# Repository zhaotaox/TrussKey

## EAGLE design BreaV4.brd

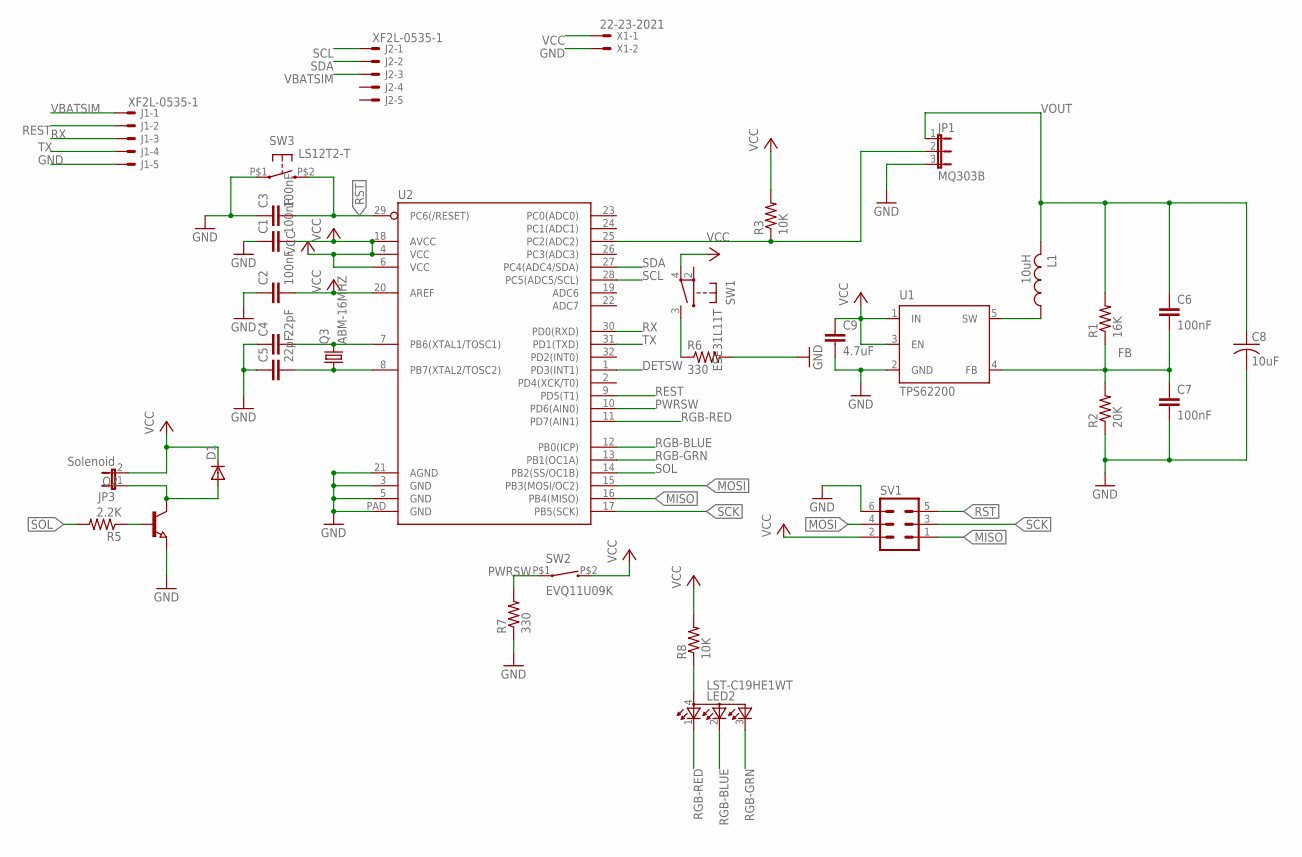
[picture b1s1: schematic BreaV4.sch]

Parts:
C1, C2, C3: 100nF; C0603
C4, C5: 22pF; C0603
C6, C7: 100nF; C0402
C8: 10uF; C0805K
C9: 4.7uF; C0402
D1: DIODE-SOD123; SOD123
J1, J2: XF2L-0535-1
JP1: MQ303B; JP2
JP3: Solenoid; JP1
L1: 10uH; L2825P
LED2: LST-C19HE1WT
Q2: NPN-TRANSISTOR_SOT23; SOT23
Q3: ABM-16MHZ
R1: 16K; R0402
R2: 20K; R0402
R3, R8: 10K; R0402
R5: 2.2K; R0402
R6, R7: 330; R0402
SV1: MA03-2
SW1: ESE31L11T; SWITCH
SW2: EVQ11U09K; EVQ11U-09K
SW3: LS12T2-T
U1: TPS62200
U2: ATMEGA328P_MLFMLF32; MLF32-PAD
X1: 22-23-2021

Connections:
DETSW: R6.1, SW1.3 (1), U2.1 (PD3(INT1))
FB: C6.2, C7.1, R1.1, R2.2, U1.4 (FB)
GND: C1.1, C2.1, C3.1, C4.1, C5.1, C7.2, C8.2, C9.2, J1.5 (MS), JP1.3, Q2.2 (E), R2.1, R6.2, R7.1, SV1.6 (MISO), SW3.P$1 (S1), U1.2 (GND), U2.3 (GND), U2.5 (GND), U2.21 (AGND), U2.PAD (GND), X1.2
MISO: SV1.1, U2.16 (PB4(MISO))
MOSI: SV1.4, U2.15 (PB3(MOSI/OC2))
unnamed: C5.2, Q3.P$1 (1), U2.8 (PB7(XTAL2/TOSC2))
unnamed: C4.2, Q3.P$2 (2), U2.7 (PB6(XTAL1/TOSC1))
unnamed: JP1.2, R3.1, U2.25 (PC2(ADC2))
unnamed: LED2.4 (A), R8.1
unnamed: D1.A, JP3.1, Q2.3 (C)
unnamed: Q2.1 (B), R5.1
PWRSW: R7.2, SW2.P$1 (1), U2.10 (PD6(AIN0))
REST: J1.2 (MS), U2.9 (PD5(T1))
RGB-BLUE: LED2.2 (CGREEN), U2.12 (PB0(ICP))
RGB-GRN: LED2.3 (CBLUE), U2.13 (PB1(OC1A))
RGB-RED: LED2.1 (CRED), U2.11 (PD7(AIN1))
RST: C3.2, SV1.5 (VTG), SW3.P$2 (S2), U2.29 (PC6(/RESET))
RX: J1.3 (MS), U2.30 (PD0(RXD))
SCK: SV1.3, U2.17 (PB5(SCK))
SCL: J2.1 (MSV), U2.28 (PC5(ADC5/SCL))
SDA: J2.2 (MS), U2.27 (PC4(ADC4/SDA))
SOL: R5.2, U2.14 (PB2(SS/OC1B))
SW: L1.1, U1.5 (SW)
TX: J1.4 (MS), U2.31 (PD1(TXD))
VBATSIM: J1.1 (MSV), J2.3 (MS)
VCC: C1.2, C2.2, C9.1, D1.C, JP3.2, R3.2, R8.2, SV1.2, SW1.4 (C3), SW2.P$2 (2), U1.1 (IN), U1.3 (EN), U2.4 (VCC), U2.6 (VCC), U2.18 (AVCC), U2.20 (AREF), X1.1
VOUT: C6.1, C8.1, JP1.1, L1.2, R1.2

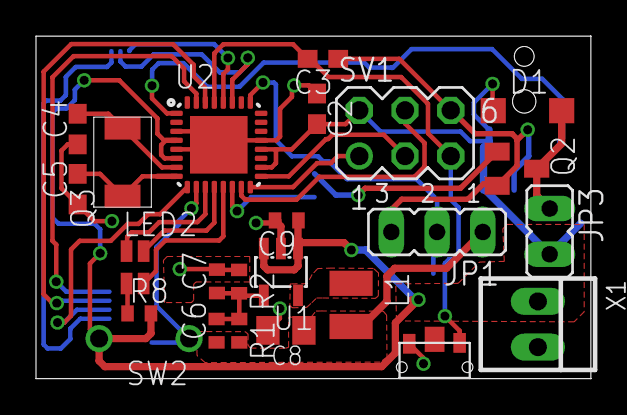
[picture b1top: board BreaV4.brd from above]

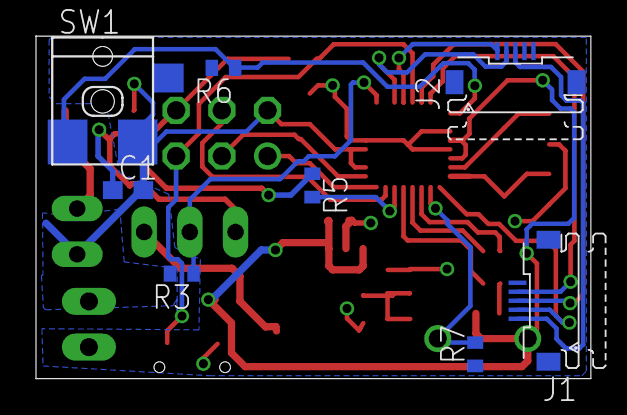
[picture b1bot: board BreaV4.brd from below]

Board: 2 copper layers, 30.8 x 19.0 mm, 32 parts (8 on the bottom side), 27 nets.

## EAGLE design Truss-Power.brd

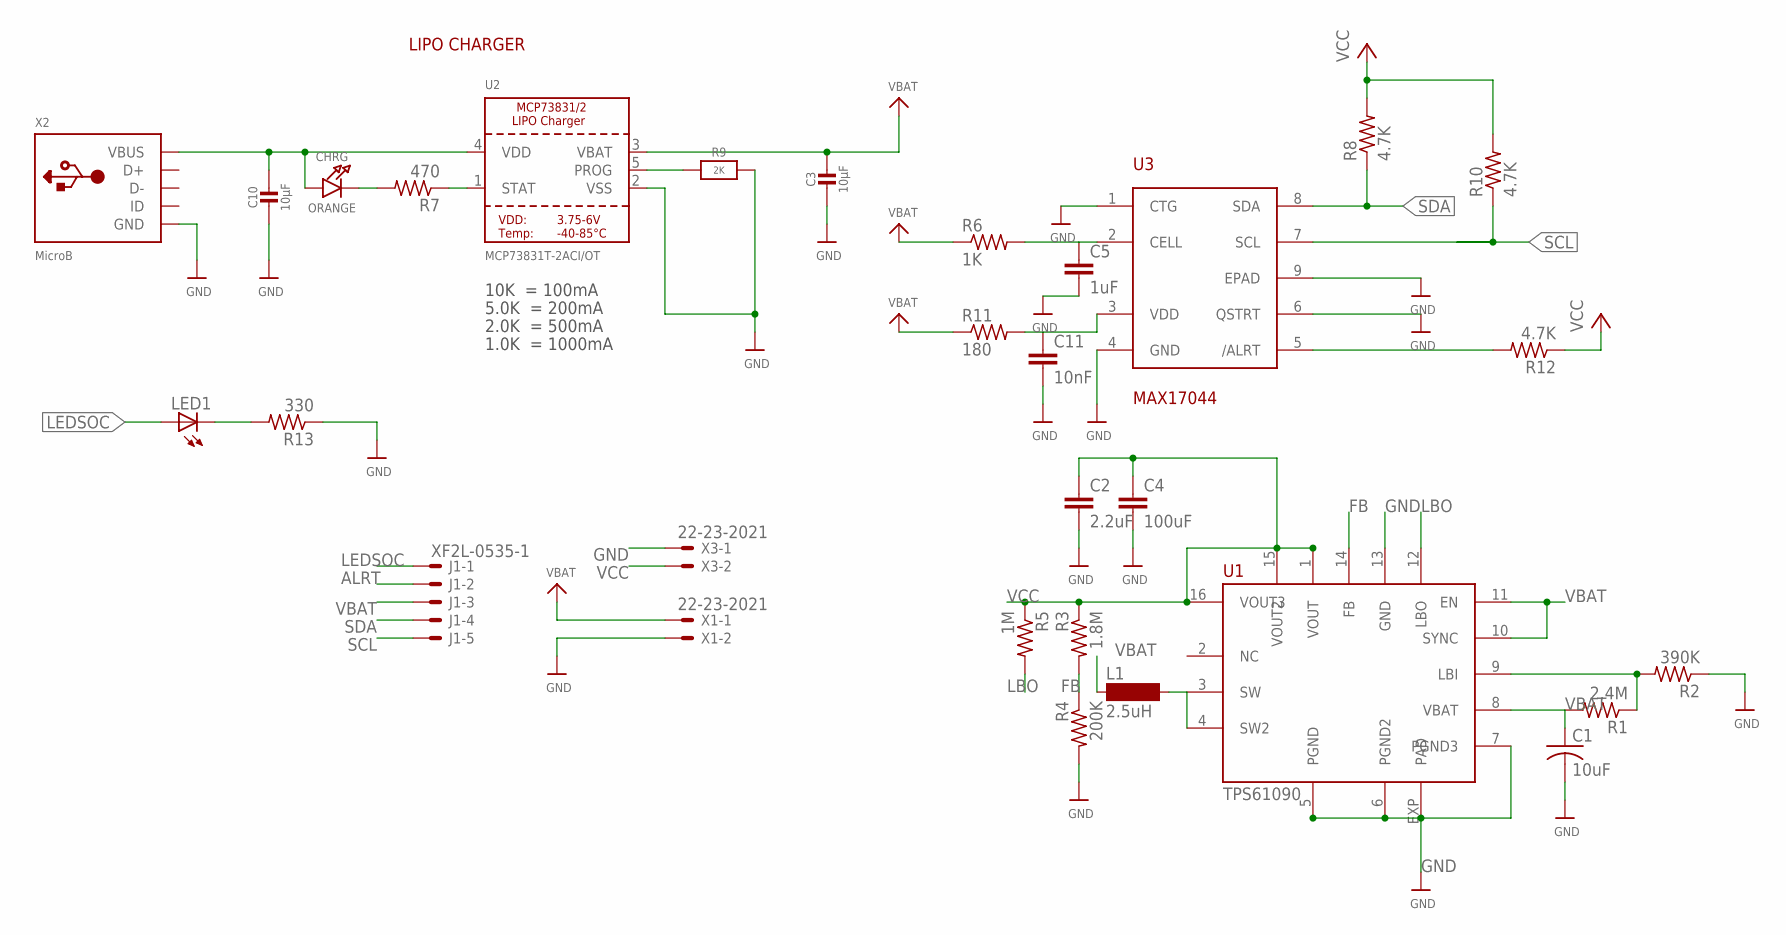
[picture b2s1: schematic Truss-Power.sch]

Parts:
C1: 10uF; C0805K
C2: 2.2uF; C0805K
C3, C10: 10µF; 0805-NO
C4: 100uF; 7343-METRIC
C5: 1uF; C0603
C11: 10nF; C0603
CHRG: ORANGE; CHIPLED_0805_NOOUTLINE
J1: XF2L-0535-1
L1: 2.5uH; CDRH5D28
LED1: LEDCHIP-LED0603; CHIP-LED0603
R1: 2.4M; R0603
R2: 390K; R0603
R3: 1.8M; R0603
R4: 200K; R0603
R5: 1M; R0603
R6: 1K; R0402
R7: 470; R0402
R8, R10, R12: 4.7K; R0402
R9: 2K; 0805-NO
R11: 180; R0402
R13: 330; R0402
U1: TPS61090
U2: MCP73831T-2ACI/OT; SOT23-5
U3: MAX17044; TDFN
X1, X3: 22-23-2021
X2: MicroB; 4UCONN_20329

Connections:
ALRT: J1.2 (MS), R12.2, U3.5 (/ALRT)
FB: R3.2, R4.1, U1.14 (FB)
GND: C1.2, C2.2, C3.2, C4.2, C5.2, C10.2, C11.2, R2.1, R4.2, R9.2, R13.1, U1.5 (PGND), U1.6 (PGND2), U1.7 (PGND3), U1.13 (GND), U1.EXP (PAD), U2.2 (VSS), U3.1 (CTG), U3.4 (GND), U3.6 (QSTRT), U3.9 (EPAD), X1.2, X2.BASE@1 (GND), X2.BASE@2 (GND), X2.GND, X2.SPRT@1 (GND), X2.SPRT@2 (GND), X2.SPRT@3 (GND), X2.SPRT@4 (GND), X3.1
LBI: R1.1, R2.2, U1.9 (LBI)
LBO: R5.2, U1.12 (LBO)
LEDSOC: J1.1 (MSV), LED1.A
unnamed: C5.1, R6.2, U3.2 (CELL)
unnamed: C11.1, R11.2, U3.3 (VDD)
unnamed: LED1.C, R13.2
unnamed: CHRG.C, R7.2
unnamed: R7.1, U2.1 (STAT)
unnamed: R9.1, U2.5 (PROG)
SCL: J1.5 (MS), R10.1, U3.7 (SCL)
SDA: J1.4 (MS), R8.1, U3.8 (SDA)
SW: L1.2, U1.3 (SW), U1.4 (SW2)
VBAT: C1.1, C3.1, J1.3 (MS), L1.1, R1.2, R6.1, R11.1, U1.8 (VBAT), U1.10 (SYNC), U1.11 (EN), U2.3 (VBAT), X1.1
VBUS: C10.1, CHRG.A, U2.4 (VDD), X2.VBUS
VCC: C2.1, C4.1, R3.1, R5.1, R8.2, R10.2, R12.1, U1.1 (VOUT), U1.15 (VOUT2), U1.16 (VOUT3), X3.2

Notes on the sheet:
10K = 100mA
5.0K = 200mA
2.0K = 500mA
1.0K = 1000mA
LIPO CHARGER

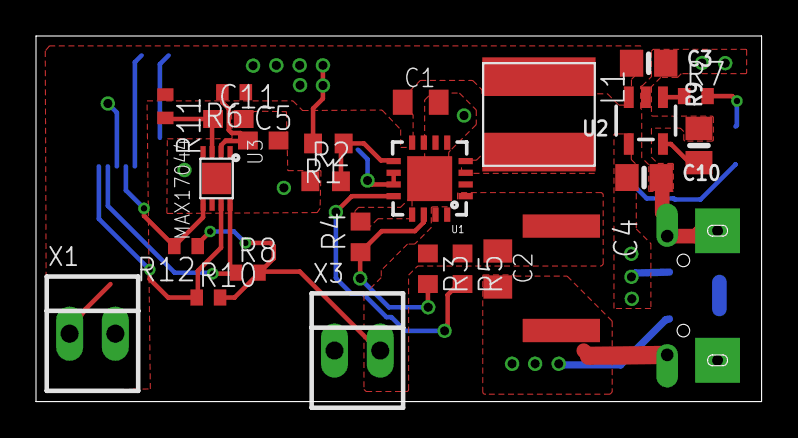
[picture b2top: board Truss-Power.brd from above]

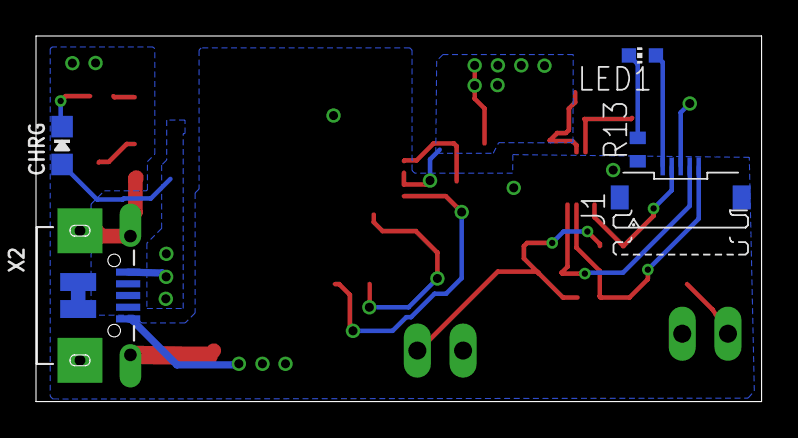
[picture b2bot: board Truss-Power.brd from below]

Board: 2 copper layers, 40.3 x 20.3 mm, 30 parts (5 on the bottom side), 18 nets.

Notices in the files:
parts and their libraries:
SparkFun-DigitalIC: Licensing: Creative Commons ShareAlike 4.0 International - https://creativecommons.org/licenses/by-sa/4.0
microbuilder: This work is placed in the public domain, and may be freely used for commercial and non-commercial work with the following conditions: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
